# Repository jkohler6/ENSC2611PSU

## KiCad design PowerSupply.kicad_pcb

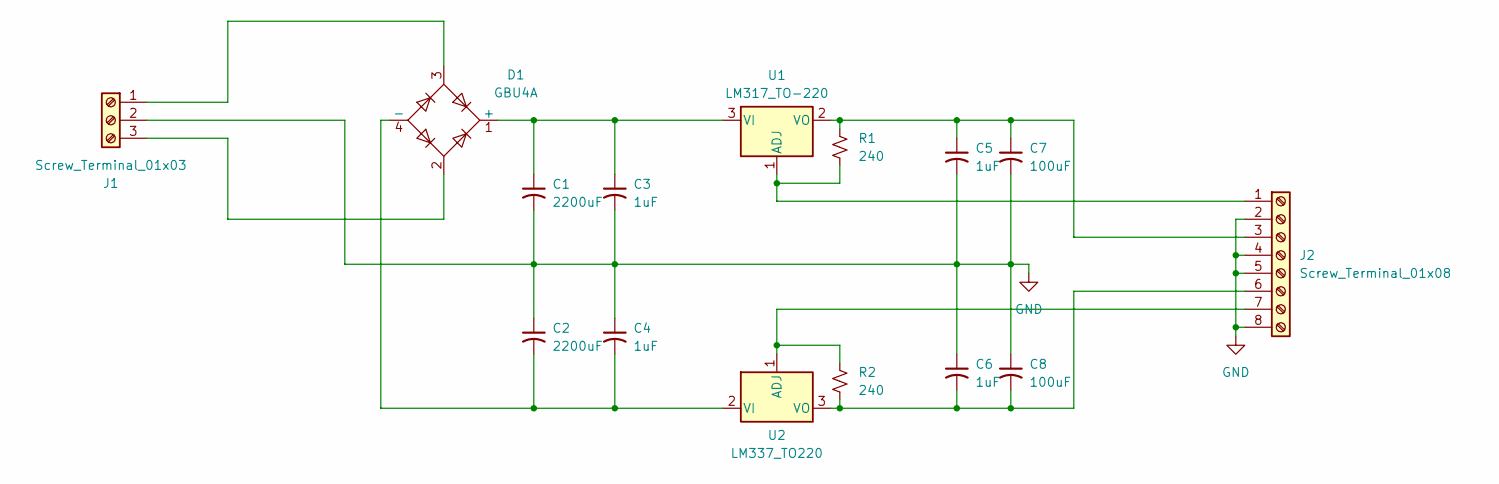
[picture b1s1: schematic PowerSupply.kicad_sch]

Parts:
C1, C2: 2200uF; CP_Radial_D10.0mm_P5.00mm
C3, C4, C5, C6: 1uF; CP_Radial_D4.0mm_P2.00mm
C7, C8: 100uF; CP_Radial_D8.0mm_P3.80mm
D1: GBU4A; Diode_Bridge_Vishay_GBU
J1: Screw_Terminal_01x03; PhoenixContact_MSTBA_2,5_3-G-5,08_1x03_P5.08mm_Horizontal
J2: Screw_Terminal_01x08; PhoenixContact_MSTBA_2,5_8-G-5,08_1x08_P5.08mm_Horizontal
R1, R2: 240; R_Axial_DIN0207_L6.3mm_D2.5mm_P15.24mm_Horizontal
U1: LM317_TO-220; TO-220-3_Vertical
U2: LM337_TO220; TO-220-3_Vertical

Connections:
GND: C1.2, C2.1, C3.2, C4.1, C5.2, C6.1, C7.2, C8.1, J1.2, J2.2, J2.4, J2.5, J2.8
unnamed: C1.1, C3.1, D1.1 (+), U1.3 (VI)
unnamed: C2.2, C4.2, D1.4 (-), U2.2 (VI)
unnamed: D1.3, J1.1
unnamed: D1.2, J1.3
unnamed: J2.1, R1.2, U1.1 (ADJ)
unnamed: C5.1, C7.1, J2.3, R1.1, U1.2 (VO)
unnamed: C6.2, C8.2, J2.6, R2.2, U2.3 (VO)
unnamed: J2.7, R2.1, U2.1 (ADJ)

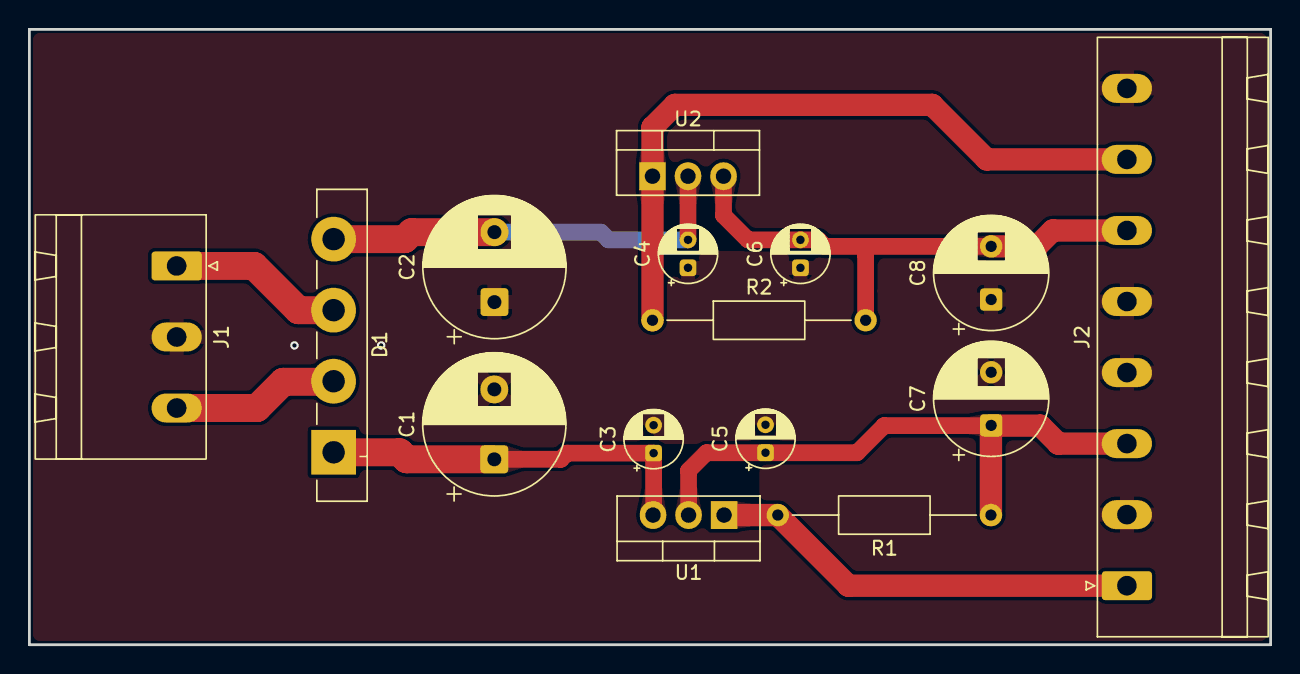
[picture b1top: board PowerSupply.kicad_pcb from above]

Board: 2 copper layers, 88.8 x 44.0 mm, 15 parts (0 on the bottom side), 9 nets.
